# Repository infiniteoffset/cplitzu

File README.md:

# Cplitzu keyboard

The Cplitzu Keyboard is a compact, ortholinear, 50-key split keyboard inspired by the [Let's split](https://github.com/nicinabox/lets-split-guide) and [Corne](https://github.com/foostan/crkbd) keyboards. It features a 3x6 ortholinear layout with an additional thumb key for improved ergonomics and functionality. Designed with ease of assembly in mind, it avoids the need for tiny SMD components, making it beginner-friendly for hand soldering.

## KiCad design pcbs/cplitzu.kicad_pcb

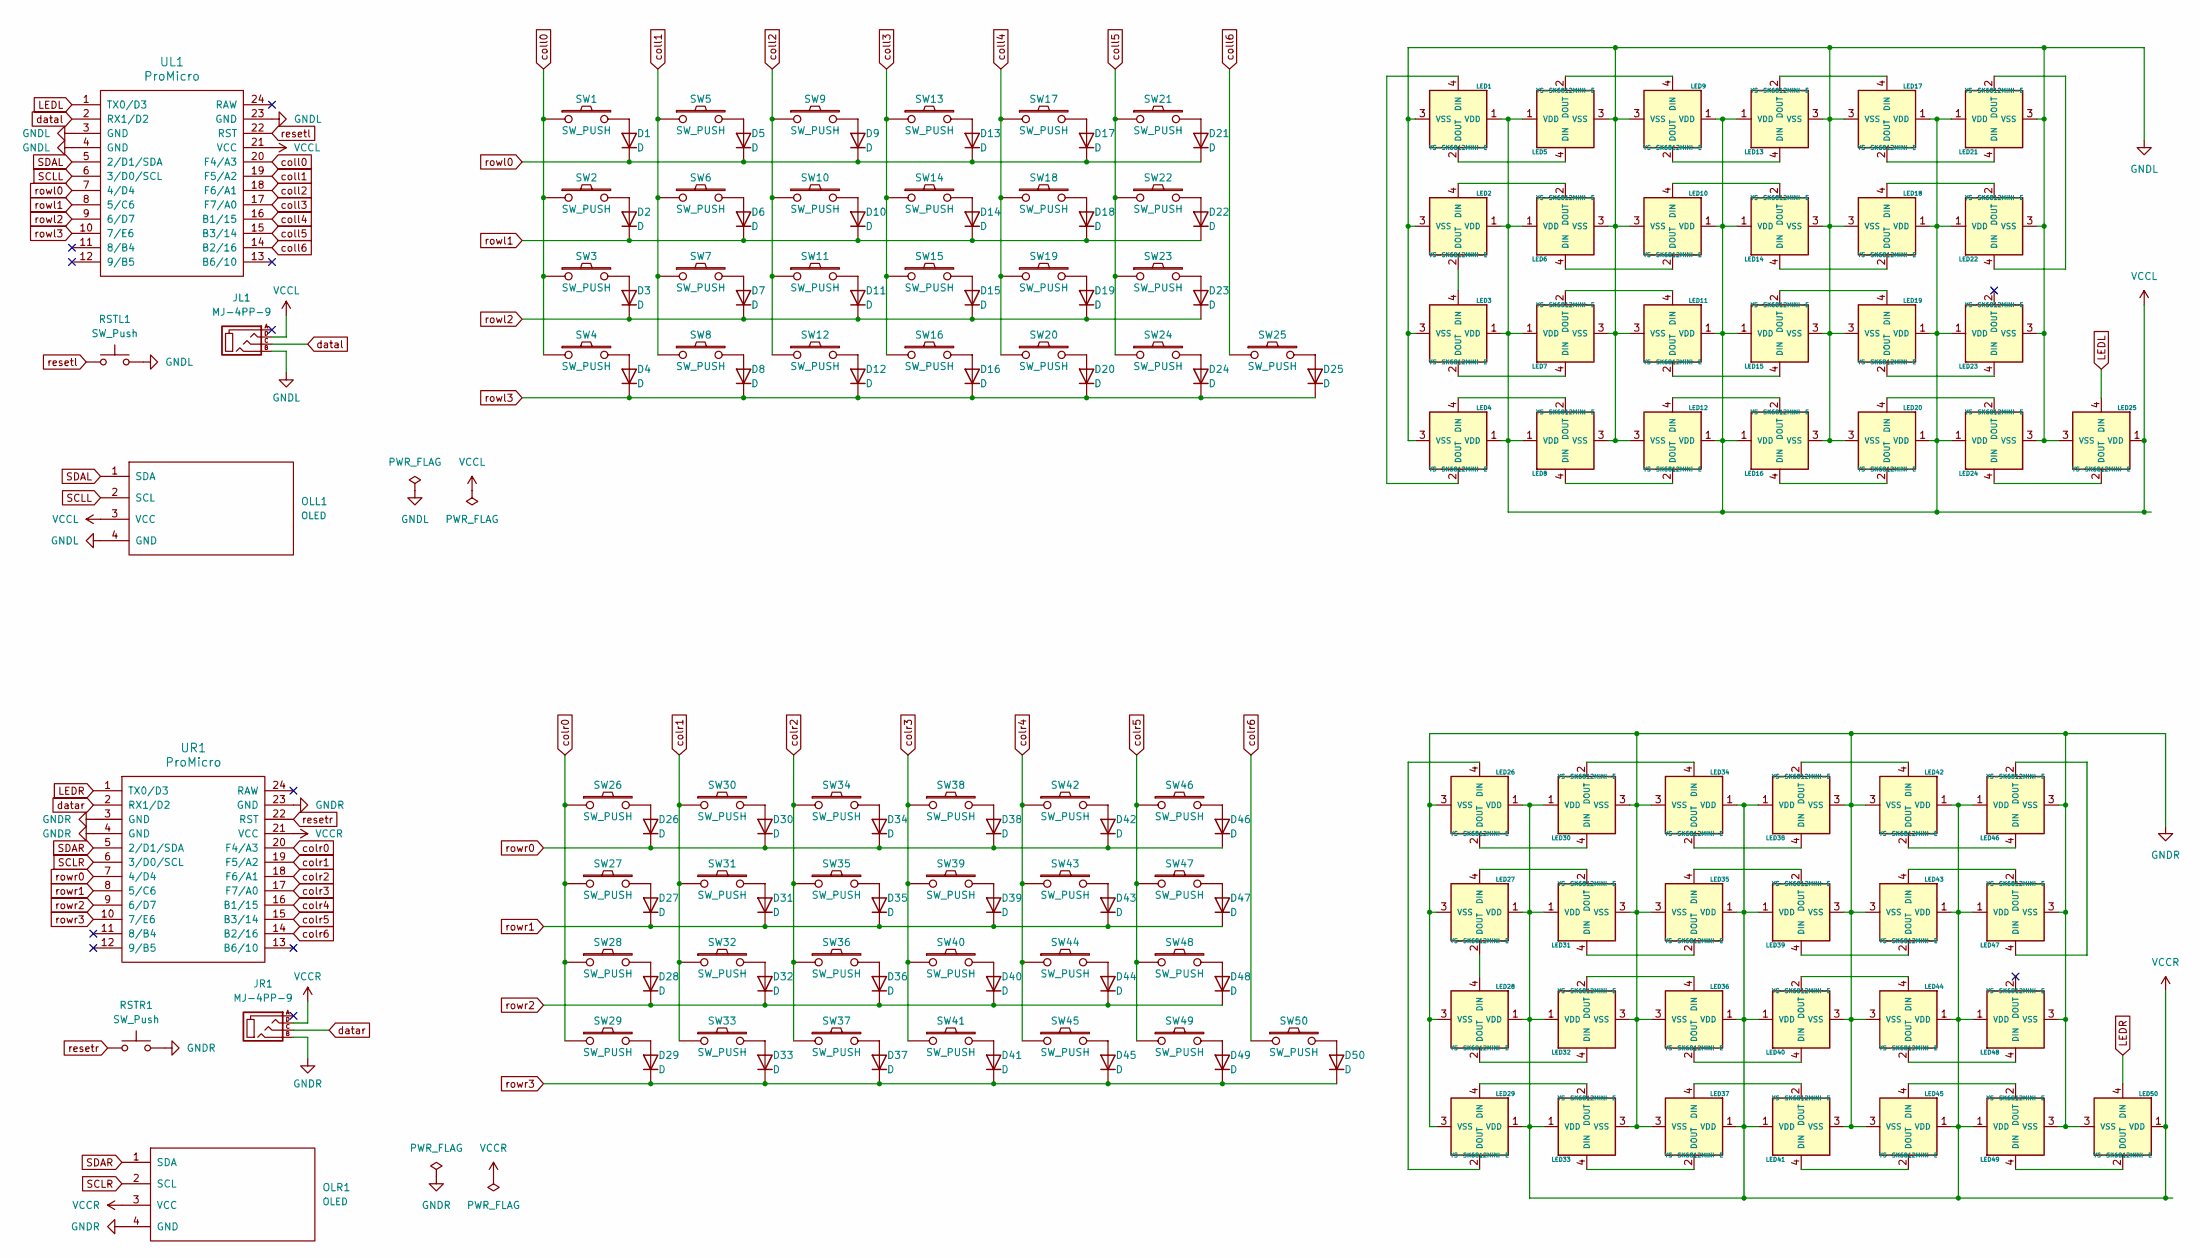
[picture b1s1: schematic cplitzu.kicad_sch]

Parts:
D1, D2, D3, D4, D5, D6, D7, D8, D9, D10, D11, D12, D13, D14, D15, D16, D17, D18, D19, D20, D21, D22, D23, D24, D25, D26, D27, D28, D29, D30, D31, D32, D33, D34, D35, D36, D37, D38, D39, D40, D41, D42, D43, D44, D45, D46, D47, D48, D49, D50: D; D_DO-35_SOD27_P7.62mm_Horizontal
JL1: MJ-4PP-9
JR1: MJ-4PP-9
LED1, LED2, LED3, LED4, LED5, LED6, LED7, LED8, LED9, LED10, LED11, LED12, LED13, LED14, LED15, LED16, LED17, LED18, LED19, LED20, LED21, LED22, LED23, LED24, LED25, LED26, LED27, LED28, LED29, LED30, LED31, LED32, LED33, LED34, LED35, LED36, LED37, LED38, LED39, LED40, LED41, LED42, LED43, LED44, LED45, LED46, LED47, LED48, LED49, LED50: YS-SK6812MINI-E
OLL1: OLED
OLR1: OLED
RSTL1: SW_Push; ResetSW
RSTR1: SW_Push; ResetSW
SW1, SW2, SW3, SW4, SW5, SW6, SW7, SW8, SW9, SW10, SW11, SW12, SW13, SW14, SW15, SW16, SW17, SW18, SW19, SW20, SW21, SW22, SW23, SW24, SW25, SW26, SW27, SW28, SW29, SW30, SW31, SW32, SW33, SW34, SW35, SW36, SW37, SW38, SW39, SW40, SW41, SW42, SW43, SW44, SW45, SW46, SW47, SW48, SW49, SW50: SW_PUSH; keyswitch_cherrymx_hotswap_1u
UL1: ProMicro
UR1: ProMicro

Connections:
GNDL: JL1.B, LED1.3 (VSS), LED2.3 (VSS), LED3.3 (VSS), LED4.3 (VSS), LED5.3 (VSS), LED6.3 (VSS), LED7.3 (VSS), LED8.3 (VSS), LED9.3 (VSS), LED10.3 (VSS), LED11.3 (VSS), LED12.3 (VSS), LED13.3 (VSS), LED14.3 (VSS), LED15.3 (VSS), LED16.3 (VSS), LED17.3 (VSS), LED18.3 (VSS), LED19.3 (VSS), LED20.3 (VSS), LED21.3 (VSS), LED22.3 (VSS), LED23.3 (VSS), LED24.3 (VSS), LED25.3 (VSS), OLL1.4 (GND), RSTL1.2, UL1.3 (GND), UL1.4 (GND), UL1.23 (GND)
GNDR: JR1.B, LED26.3 (VSS), LED27.3 (VSS), LED28.3 (VSS), LED29.3 (VSS), LED30.3 (VSS), LED31.3 (VSS), LED32.3 (VSS), LED33.3 (VSS), LED34.3 (VSS), LED35.3 (VSS), LED36.3 (VSS), LED37.3 (VSS), LED38.3 (VSS), LED39.3 (VSS), LED40.3 (VSS), LED41.3 (VSS), LED42.3 (VSS), LED43.3 (VSS), LED44.3 (VSS), LED45.3 (VSS), LED46.3 (VSS), LED47.3 (VSS), LED48.3 (VSS), LED49.3 (VSS), LED50.3 (VSS), OLR1.4 (GND), RSTR1.2, UR1.3 (GND), UR1.4 (GND), UR1.23 (GND)
LEDL: LED25.4 (DIN), UL1.1 (TX0/D3)
LEDR: LED50.4 (DIN), UR1.1 (TX0/D3)
unnamed: D1.2 (A), SW1.2
unnamed: D2.2 (A), SW2.2
unnamed: D3.2 (A), SW3.2
unnamed: D4.2 (A), SW4.2
unnamed: D5.2 (A), SW5.2
unnamed: D6.2 (A), SW6.2
unnamed: D7.2 (A), SW7.2
unnamed: D8.2 (A), SW8.2
unnamed: D9.2 (A), SW9.2
unnamed: D10.2 (A), SW10.2
unnamed: D11.2 (A), SW11.2
unnamed: D12.2 (A), SW12.2
unnamed: D13.2 (A), SW13.2
unnamed: D14.2 (A), SW14.2
unnamed: D15.2 (A), SW15.2
unnamed: D16.2 (A), SW16.2
unnamed: D17.2 (A), SW17.2
unnamed: D18.2 (A), SW18.2
unnamed: D19.2 (A), SW19.2
unnamed: D20.2 (A), SW20.2
unnamed: D21.2 (A), SW21.2
unnamed: D22.2 (A), SW22.2
unnamed: D23.2 (A), SW23.2
unnamed: D24.2 (A), SW24.2
unnamed: D25.2 (A), SW25.2
unnamed: D26.2 (A), SW26.2
unnamed: D27.2 (A), SW27.2
unnamed: D28.2 (A), SW28.2
unnamed: D29.2 (A), SW29.2
unnamed: D30.2 (A), SW30.2
unnamed: D31.2 (A), SW31.2
unnamed: D32.2 (A), SW32.2
unnamed: D33.2 (A), SW33.2
unnamed: D34.2 (A), SW34.2
unnamed: D35.2 (A), SW35.2
unnamed: D36.2 (A), SW36.2
unnamed: D37.2 (A), SW37.2
unnamed: D38.2 (A), SW38.2
unnamed: D39.2 (A), SW39.2
unnamed: D40.2 (A), SW40.2
unnamed: D41.2 (A), SW41.2
unnamed: D42.2 (A), SW42.2
unnamed: D43.2 (A), SW43.2
unnamed: D44.2 (A), SW44.2
unnamed: D45.2 (A), SW45.2
unnamed: D46.2 (A), SW46.2
unnamed: D47.2 (A), SW47.2
unnamed: D48.2 (A), SW48.2
unnamed: D49.2 (A), SW49.2
unnamed: D50.2 (A), SW50.2
unnamed: LED1.4 (DIN), LED4.2 (DOUT)
unnamed: LED1.2 (DOUT), LED5.4 (DIN)
unnamed: LED2.4 (DIN), LED6.2 (DOUT)
unnamed: LED2.2 (DOUT), LED3.4 (DIN)
unnamed: LED3.2 (DOUT), LED7.4 (DIN)
unnamed: LED4.4 (DIN), LED8.2 (DOUT)
unnamed: LED5.2 (DOUT), LED9.4 (DIN)
unnamed: LED10.4 (DIN), LED14.2 (DOUT)
unnamed: LED6.4 (DIN), LED10.2 (DOUT)
unnamed: LED7.2 (DOUT), LED11.4 (DIN)
unnamed: LED11.2 (DOUT), LED15.4 (DIN)
unnamed: LED12.4 (DIN), LED16.2 (DOUT)
unnamed: LED8.4 (DIN), LED12.2 (DOUT)
unnamed: LED9.2 (DOUT), LED13.4 (DIN)
unnamed: LED13.2 (DOUT), LED17.4 (DIN)
unnamed: LED14.4 (DIN), LED18.2 (DOUT)
unnamed: LED15.2 (DOUT), LED19.4 (DIN)
unnamed: LED16.4 (DIN), LED20.2 (DOUT)
unnamed: LED17.2 (DOUT), LED21.4 (DIN)
unnamed: LED18.4 (DIN), LED22.2 (DOUT)
unnamed: LED19.2 (DOUT), LED23.4 (DIN)
unnamed: LED20.4 (DIN), LED24.2 (DOUT)
unnamed: LED21.2 (DOUT), LED22.4 (DIN)
unnamed: LED24.4 (DIN), LED25.2 (DOUT)
unnamed: LED26.4 (DIN), LED29.2 (DOUT)
unnamed: LED26.2 (DOUT), LED30.4 (DIN)
unnamed: LED27.4 (DIN), LED31.2 (DOUT)
unnamed: LED27.2 (DOUT), LED28.4 (DIN)
unnamed: LED28.2 (DOUT), LED32.4 (DIN)
unnamed: LED29.4 (DIN), LED33.2 (DOUT)
unnamed: LED30.2 (DOUT), LED34.4 (DIN)
unnamed: LED31.4 (DIN), LED35.2 (DOUT)
unnamed: LED32.2 (DOUT), LED36.4 (DIN)
unnamed: LED33.4 (DIN), LED37.2 (DOUT)
unnamed: LED34.2 (DOUT), LED38.4 (DIN)
unnamed: LED35.4 (DIN), LED39.2 (DOUT)
unnamed: LED36.2 (DOUT), LED40.4 (DIN)
unnamed: LED37.4 (DIN), LED41.2 (DOUT)
unnamed: LED38.2 (DOUT), LED42.4 (DIN)
unnamed: LED39.4 (DIN), LED43.2 (DOUT)
unnamed: LED40.2 (DOUT), LED44.4 (DIN)
unnamed: LED41.4 (DIN), LED45.2 (DOUT)
unnamed: LED42.2 (DOUT), LED46.4 (DIN)
unnamed: LED43.4 (DIN), LED47.2 (DOUT)
unnamed: LED44.2 (DOUT), LED48.4 (DIN)
unnamed: LED45.4 (DIN), LED49.2 (DOUT)
unnamed: LED46.2 (DOUT), LED47.4 (DIN)
unnamed: LED49.4 (DIN), LED50.2 (DOUT)
SCLL: OLL1.2 (SCL), UL1.6 (3/D0/SCL)
SCLR: OLR1.2 (SCL), UR1.6 (3/D0/SCL)
SDAL: OLL1.1 (SDA), UL1.5 (2/D1/SDA)
SDAR: OLR1.1 (SDA), UR1.5 (2/D1/SDA)
VCCL: JL1.D, LED1.1 (VDD), LED2.1 (VDD), LED3.1 (VDD), LED4.1 (VDD), LED5.1 (VDD), LED6.1 (VDD), LED7.1 (VDD), LED8.1 (VDD), LED9.1 (VDD), LED10.1 (VDD), LED11.1 (VDD), LED12.1 (VDD), LED13.1 (VDD), LED14.1 (VDD), LED15.1 (VDD), LED16.1 (VDD), LED17.1 (VDD), LED18.1 (VDD), LED19.1 (VDD), LED20.1 (VDD), LED21.1 (VDD), LED22.1 (VDD), LED23.1 (VDD), LED24.1 (VDD), LED25.1 (VDD), OLL1.3 (VCC), UL1.21 (VCC)
VCCR: JR1.D, LED26.1 (VDD), LED27.1 (VDD), LED28.1 (VDD), LED29.1 (VDD), LED30.1 (VDD), LED31.1 (VDD), LED32.1 (VDD), LED33.1 (VDD), LED34.1 (VDD), LED35.1 (VDD), LED36.1 (VDD), LED37.1 (VDD), LED38.1 (VDD), LED39.1 (VDD), LED40.1 (VDD), LED41.1 (VDD), LED42.1 (VDD), LED43.1 (VDD), LED44.1 (VDD), LED45.1 (VDD), LED46.1 (VDD), LED47.1 (VDD), LED48.1 (VDD), LED49.1 (VDD), LED50.1 (VDD), OLR1.3 (VCC), UR1.21 (VCC)
coll0: SW1.1, SW2.1, SW3.1, SW4.1, UL1.20 (F4/A3)
coll1: SW5.1, SW6.1, SW7.1, SW8.1, UL1.19 (F5/A2)
coll2: SW9.1, SW10.1, SW11.1, SW12.1, UL1.18 (F6/A1)
coll3: SW13.1, SW14.1, SW15.1, SW16.1, UL1.17 (F7/A0)
coll4: SW17.1, SW18.1, SW19.1, SW20.1, UL1.16 (B1/15)
coll5: SW21.1, SW22.1, SW23.1, SW24.1, UL1.15 (B3/14)
coll6: SW25.1, UL1.14 (B2/16)
colr0: SW26.1, SW27.1, SW28.1, SW29.1, UR1.20 (F4/A3)
colr1: SW30.1, SW31.1, SW32.1, SW33.1, UR1.19 (F5/A2)
colr2: SW34.1, SW35.1, SW36.1, SW37.1, UR1.18 (F6/A1)
colr3: SW38.1, SW39.1, SW40.1, SW41.1, UR1.17 (F7/A0)
colr4: SW42.1, SW43.1, SW44.1, SW45.1, UR1.16 (B1/15)
colr5: SW46.1, SW47.1, SW48.1, SW49.1, UR1.15 (B3/14)
colr6: SW50.1, UR1.14 (B2/16)
datal: JL1.C, UL1.2 (RX1/D2)
datar: JR1.C, UR1.2 (RX1/D2)
resetl: RSTL1.1, UL1.22 (RST)
resetr: RSTR1.1, UR1.22 (RST)
rowl0: D1.1 (K), D5.1 (K), D9.1 (K), D13.1 (K), D17.1 (K), D21.1 (K), UL1.7 (4/D4)
rowl1: D2.1 (K), D6.1 (K), D10.1 (K), D14.1 (K), D18.1 (K), D22.1 (K), UL1.8 (5/C6)
rowl2: D3.1 (K), D7.1 (K), D11.1 (K), D15.1 (K), D19.1 (K), D23.1 (K), UL1.9 (6/D7)
rowl3: D4.1 (K), D8.1 (K), D12.1 (K), D16.1 (K), D20.1 (K), D24.1 (K), D25.1 (K), UL1.10 (7/E6)
rowr0: D26.1 (K), D30.1 (K), D34.1 (K), D38.1 (K), D42.1 (K), D46.1 (K), UR1.7 (4/D4)
rowr1: D27.1 (K), D31.1 (K), D35.1 (K), D39.1 (K), D43.1 (K), D47.1 (K), UR1.8 (5/C6)
rowr2: D28.1 (K), D32.1 (K), D36.1 (K), D40.1 (K), D44.1 (K), D48.1 (K), UR1.9 (6/D7)
rowr3: D29.1 (K), D33.1 (K), D37.1 (K), D41.1 (K), D45.1 (K), D49.1 (K), D50.1 (K), UR1.10 (7/E6)

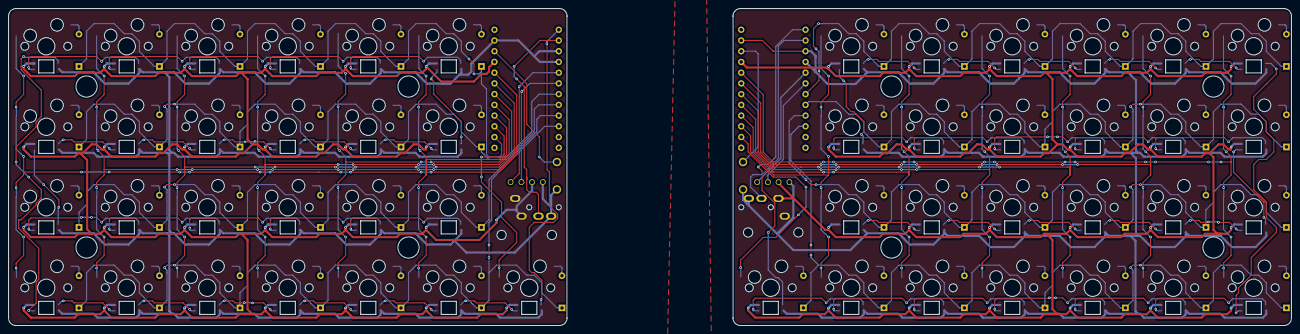
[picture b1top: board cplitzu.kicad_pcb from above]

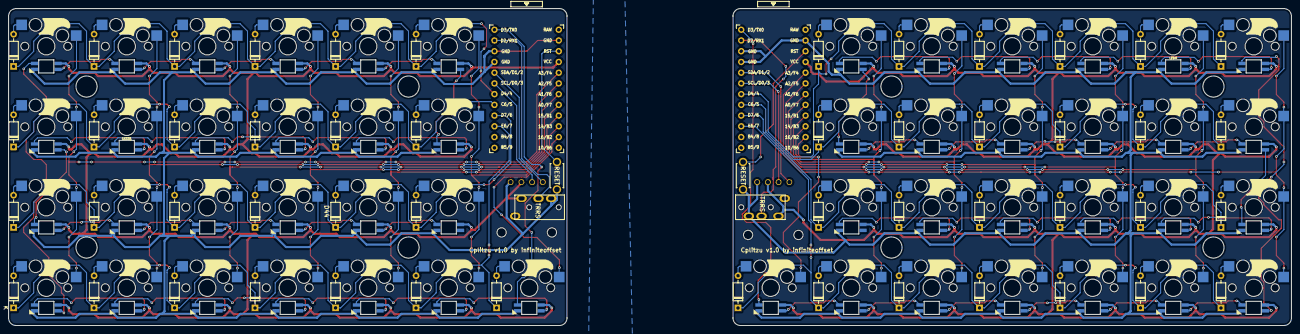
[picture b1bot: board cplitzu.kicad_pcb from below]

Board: 2 copper layers, 303.6 x 75.0 mm, 158 parts (150 on the bottom side), 134 nets.

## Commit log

2025-01-29 update license
2025-01-30 rename gerbers
2025-01-30 create plates
2025-01-31 create cases
2025-02-11 change case dimensions and remove feet holes
2025-02-11 add oled cover
